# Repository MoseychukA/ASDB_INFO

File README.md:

# ASDB_INFO
Исходные файлы ADSB декодера

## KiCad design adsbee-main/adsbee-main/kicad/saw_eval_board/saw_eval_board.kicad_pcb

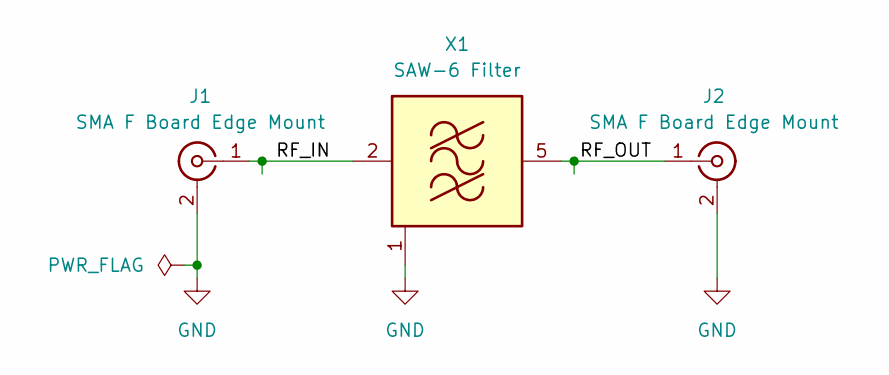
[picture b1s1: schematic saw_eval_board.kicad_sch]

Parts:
J1, J2: SMA F Board Edge Mount; SMA_Amphenol_132289_EdgeMount
X1: SAW-6 Filter; Filter_SAW-6_3.0x3.0mm

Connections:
/RF_IN: J1.1 (In), X1.2 (IN)
/RF_OUT: J2.1 (In), X1.5 (OUT)
GND: J1.2 (Ext), J2.2 (Ext), X1.1 (GND), X1.3 (GND), X1.4 (GND), X1.6 (GND)

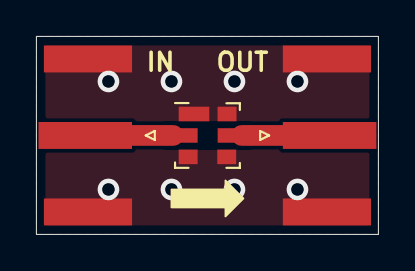
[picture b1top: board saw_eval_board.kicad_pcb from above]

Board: 2 copper layers, 19.0 x 11.0 mm, 3 parts (0 on the bottom side), 3 nets.

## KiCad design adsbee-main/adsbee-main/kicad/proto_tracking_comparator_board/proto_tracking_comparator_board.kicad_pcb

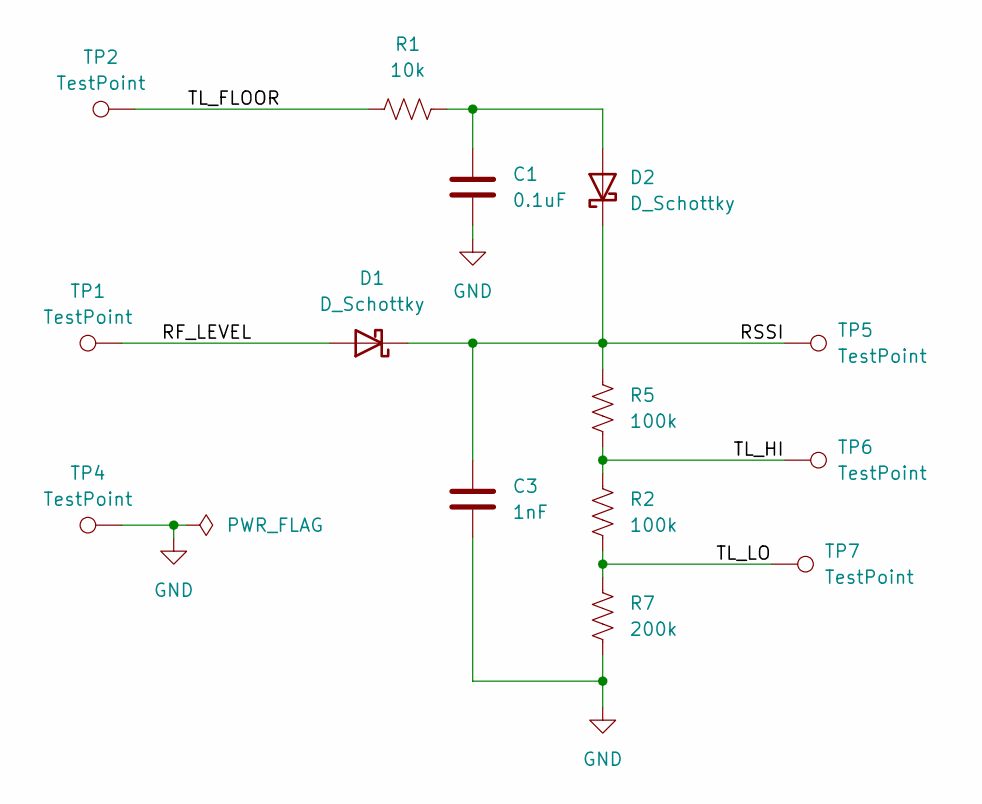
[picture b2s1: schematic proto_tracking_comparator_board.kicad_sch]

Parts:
C1: 0.1uF; C_0603_1608Metric
C3: 1nF; C_0603_1608Metric
D1, D2: D_Schottky; D_0402_1005Metric
R1: 10k; R_0603_1608Metric
R2, R5: 100k; R_0603_1608Metric
R7: 200k; R_0603_1608Metric
TP1, TP2, TP4, TP5, TP6, TP7: TestPoint; TestPoint_Pad_1.0x1.0mm

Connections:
/RF_LEVEL: D1.2 (A), TP1.1
/RSSI: C3.1, D1.1 (K), D2.1 (K), R5.2, TP5.1
/TL_FLOOR: R1.2, TP2.1
/TL_HI: R2.2, R5.1, TP6.1
/TL_LO: R2.1, R7.2, TP7.1
GND: C1.2, C3.2, R7.1, TP4.1
unnamed: C1.1, D2.2 (A), R1.1

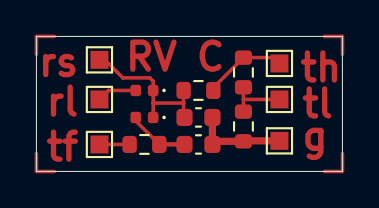
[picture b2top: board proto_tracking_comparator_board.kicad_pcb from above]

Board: 2 copper layers, 17.0 x 7.5 mm, 14 parts (0 on the bottom side), 7 nets.

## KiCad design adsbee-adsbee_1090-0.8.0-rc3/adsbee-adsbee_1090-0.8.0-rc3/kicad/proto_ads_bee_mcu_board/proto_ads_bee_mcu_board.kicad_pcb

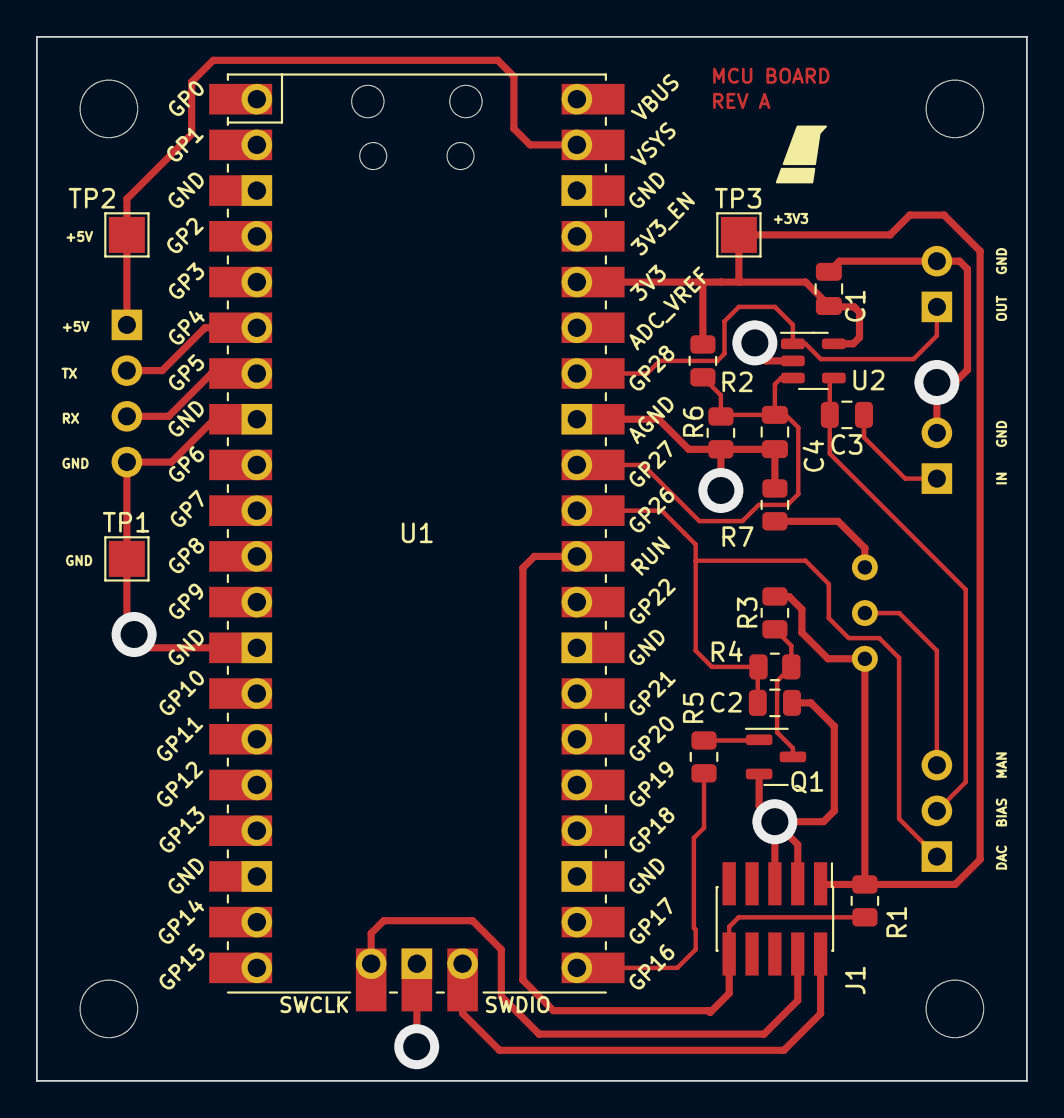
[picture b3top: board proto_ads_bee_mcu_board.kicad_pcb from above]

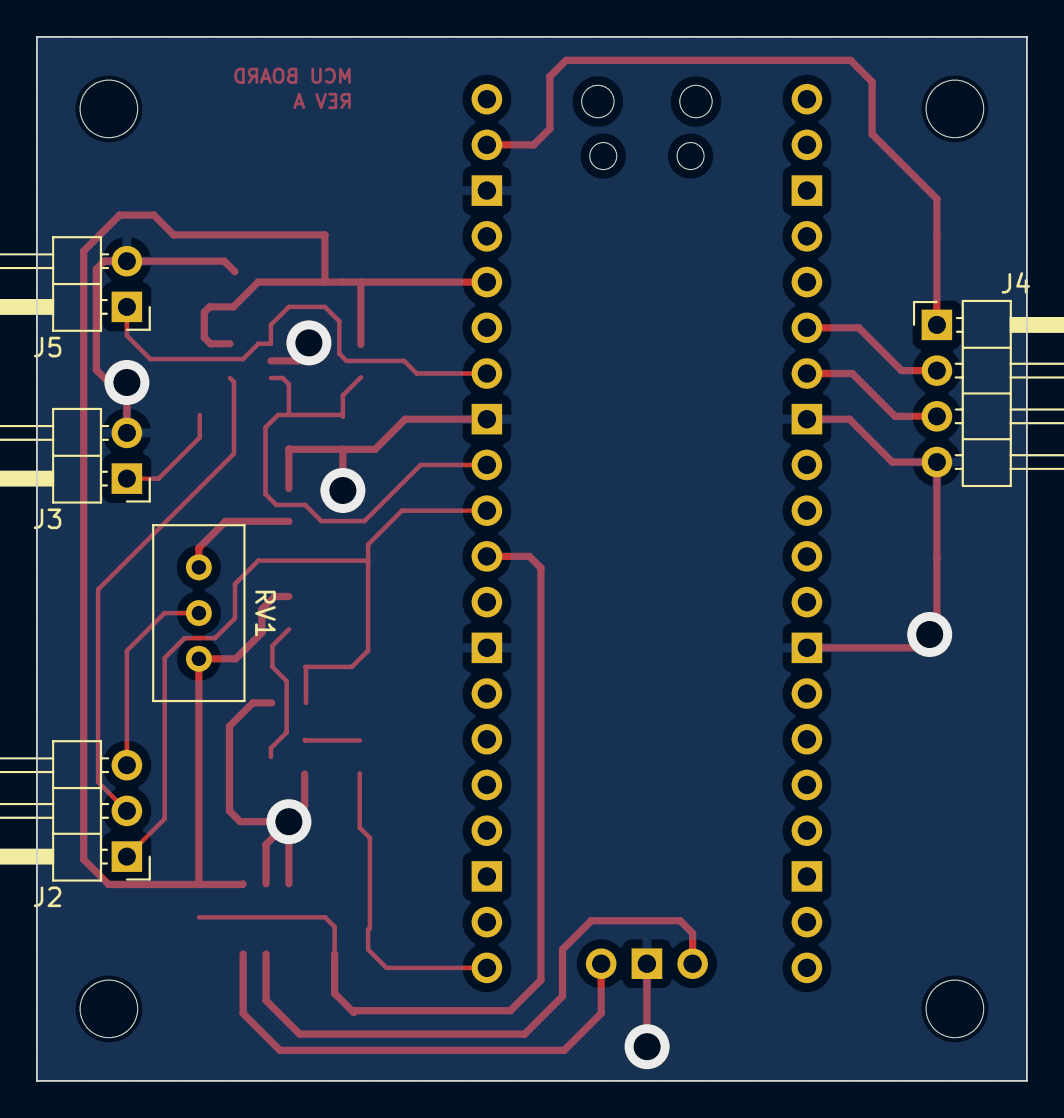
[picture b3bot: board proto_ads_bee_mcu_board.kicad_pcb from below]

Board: 2 copper layers, 55.0 x 58.0 mm, 29 parts (5 on the bottom side), 18 nets.

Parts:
C1, C2, C4: 0.1uF; C_0805_2012Metric
C3: 1uF; C_0805_2012Metric
GRAPHIC1: Graphic; bird_with_pants_small_flipped
H1, H2, H3, H4: MountingHole; MountingHole_3.2mm_M3
J1: Conn_ARM_JTAG_SWD_10; PinHeader_2x05_P1.27mm_Vertical_SMD
J2: Conn_01x03_Pin; PinHeader_1x03_P2.54mm_Horizontal
J3, J5: Conn_01x02_Pin; PinHeader_1x02_P2.54mm_Horizontal
J4: Conn_01x04_Pin; PinHeader_1x04_P2.54mm_Horizontal
PCB1: PCB; PCB_PN_REV_small
Q1: 2N7002; SOT-23
R1, R2, R4: 10k; R_0805_2012Metric
R3: 1k; R_0805_2012Metric
R5: 100; R_0805_2012Metric
R6, R7: 4.99k; R_0805_2012Metric
RV1: 10k; Potentiometer_Bourns_3296W_Vertical
TP1, TP2, TP3: TestPoint; TestPoint_Pad_2.0x2.0mm
U1: Pico; RPi_Pico_SMD_TH
U2: MCP6541; SOT-23-5

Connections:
+3V3: C1.1, J1.1 (VTref), R1.1, R2.1, R3.1, RV1.1, TP3.1, U1.36 (3V3), U2.5 (V+)
+5V: J4.1, TP2.1, U1.39 (VSYS)
/COMP_BIAS_DC: C2.1, J2.1, R4.2, U1.31 (GPIO26_ADC0)
/COMP_BIAS_PWM: R5.1, U1.21 (GPIO16)
/COMP_OUT: J5.1, U1.34 (GPIO28_ADC2), U2.1
/COMP_REF: C4.1, R2.2, R6.1, U1.32 (GPIO27_ADC1), U2.3 (+)
/COMP_SIG: C3.2, J2.2, U2.4 (-)
/UART_RX: J4.3, U1.7 (GPIO5)
/UART_TX: J4.2, U1.6 (GPIO4)
/V_DN: C3.1, J3.1
/~RESET: J1.10 (~RESET), R1.2, U1.30 (RUN)
GND: C1.2, C2.2, C4.2, J1.3 (GND), J1.5 (GND), J3.2, J4.4, J5.2, Q1.2 (S), R6.2, R7.2, TP1.1, U1.8 (GND), U1.13 (GND), U1.28 (GND), U1.33 (AGND), U1.38 (GND), U1.42 (GND), U2.2 (V-)
unnamed: J1.4 (SWDCLK/TCK), U1.41 (SWCLK)
unnamed: J1.2 (SWDIO/TMS), U1.43 (SWDIO)
unnamed: J2.3, RV1.2
unnamed: Q1.3 (D), R3.2, R4.1
unnamed: Q1.1 (G), R5.2
unnamed: R7.1, RV1.3

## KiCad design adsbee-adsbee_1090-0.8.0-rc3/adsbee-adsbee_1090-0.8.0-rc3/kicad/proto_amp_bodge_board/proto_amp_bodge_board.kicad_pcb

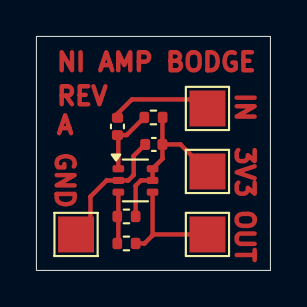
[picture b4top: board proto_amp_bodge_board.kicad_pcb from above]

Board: 2 copper layers, 13.0 x 13.0 mm, 10 parts (0 on the bottom side), 6 nets.

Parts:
C1: 0.1uF; C_0402_1005Metric
C2: 22nF; C_0402_1005Metric
R1, R2: 10k; R_0402_1005Metric
R3: 100k; R_0402_1005Metric
TP1, TP2, TP3, TP4: TestPoint; TestPoint_Pad_2.0x2.0mm
U1: OPA358AIDCKR; SOT-363_SC-70-6

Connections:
+3V3: C1.1, R1.1, R2.1, TP3.1, U1.5 (ENABLE), U1.6 (V+)
GND: C1.2, TP4.1, U1.2 (V-)
unnamed: C2.1, TP2.1
unnamed: R3.2, TP1.1, U1.4
unnamed: C2.2, R1.2, U1.1 (+)
unnamed: R2.2, R3.1, U1.3 (-)

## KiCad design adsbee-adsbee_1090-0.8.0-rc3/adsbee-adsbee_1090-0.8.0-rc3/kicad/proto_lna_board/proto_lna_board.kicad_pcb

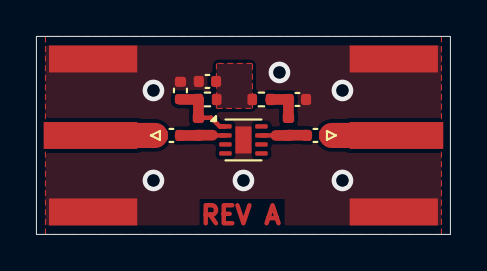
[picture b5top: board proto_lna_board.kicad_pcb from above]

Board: 2 copper layers, 23.0 x 11.0 mm, 12 parts (0 on the bottom side), 8 nets.

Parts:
C1: 0.1uF; C_0402_1005Metric
C2, C5: 12pF; C_0402_1005Metric
C3, C4: 100pF; C_0402_1005Metric
J1, J2: SMA Female Edge Mount; SMA_Amphenol_132289_EdgeMount
L1: 27nH RF; L_0402_1005Metric
L2: 82nH RF; L_0402_1005Metric
R1: 6.8k; R_0402_1005Metric
R2: 0R; R_0402_1005Metric
U1: BLB01; DFN-8-1EP_2x2mm_P0.5mm_EP0.9x1.5mm

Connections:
+3V3: C1.1, R1.1, R2.1
/RF_IN: C4.1, J1.1 (In)
/RF_IN': C4.2, L1.2, U1.2
/RF_OUT: C5.2, J2.1 (In)
/RF_OUT': C5.1, L2.2, U1.7
GND: C1.2, C2.1, C3.2, J1.2 (Ext), J2.2 (Ext), U1.9 (G)
unnamed: C3.1, L2.1, R2.2
unnamed: C2.2, L1.1, R1.2, U1.1 (Vcc)
